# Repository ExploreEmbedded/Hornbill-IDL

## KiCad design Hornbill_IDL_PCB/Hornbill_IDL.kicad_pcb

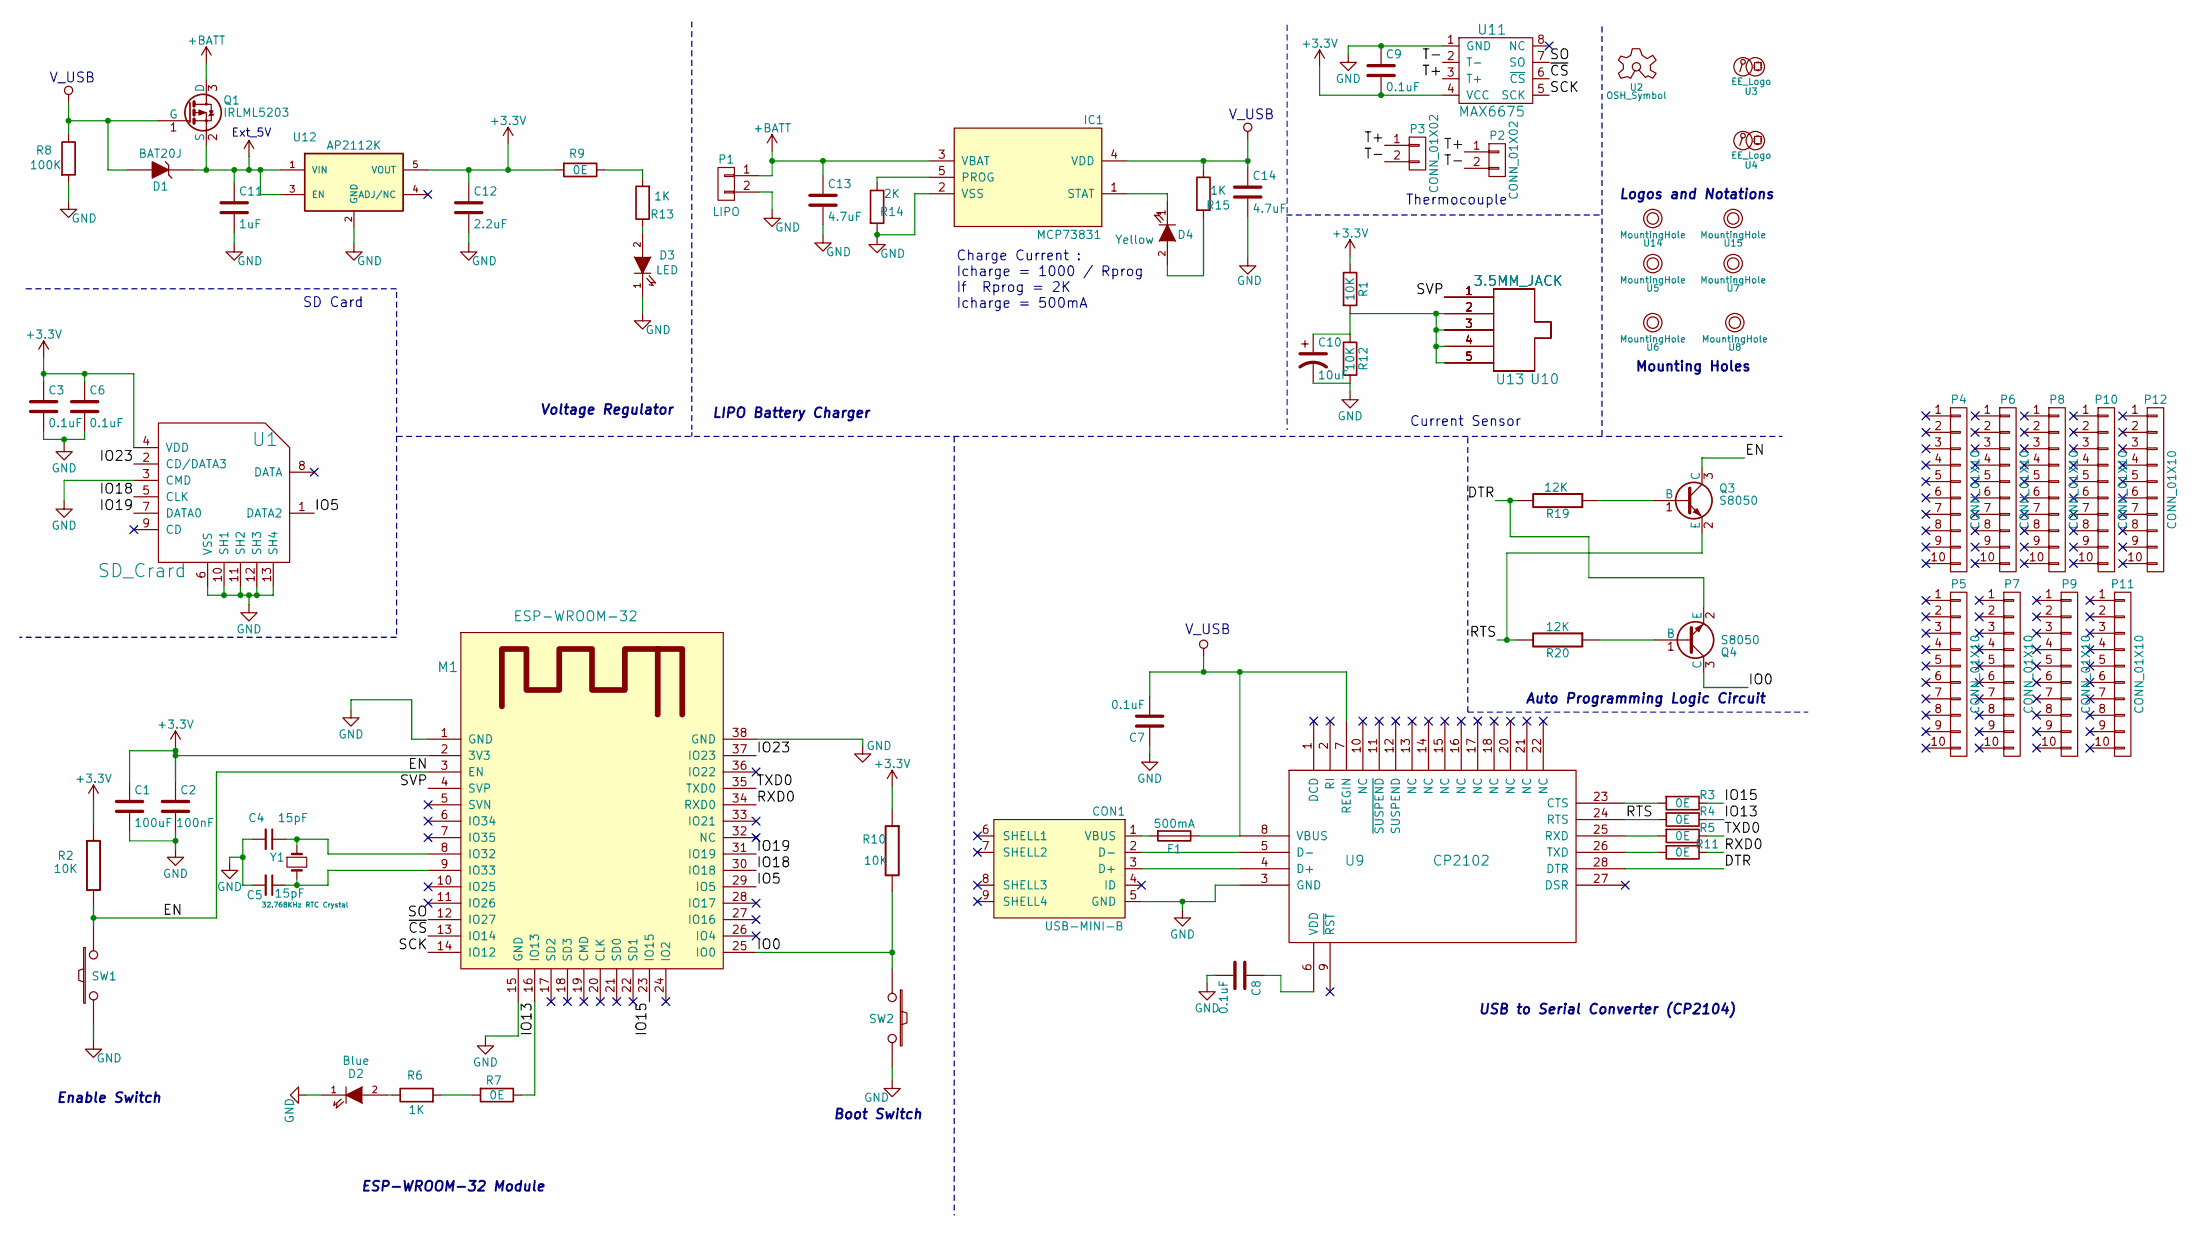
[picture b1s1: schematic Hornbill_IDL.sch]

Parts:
C1: 100uF; C_1206
C2: 100nF; C_0603
C3, C6, C7, C8: 0.1uF; C_0603
C4, C5: 15pF; C_0603
C9: 0.1uF; C_1206
C10: 10uF; CP_Radial_D4.0mm_P2.00mm
C11: 1uF; C_0603
C12: 2.2uF; C_0603
C13, C14: 4.7uF; C_0603
CON1: USB-MINI-B; USB_Micro-B_SMD_NEW_1
D1: BAT20J; SOD-80_diode_1
D2: Blue; LED-0603_NEW
D3: LED; LED-0603
D4: Yellow; LED-0603
F1: 500mA; Fuse_500mA
IC1: MCP73831; SOT-23-5
M1: ESP-WROOM-32; ESP-32S
P1: LIPO; JST_SMD
P2, P3: CONN_01X02; Thermocouple Connector
P4, P5, P6, P7, P8, P9, P10, P11, P12: CONN_01X10; Pin_Header_Straight_1x10_Pitch2.54mm
Q1: IRLML5203; SOT-23
Q3, Q4: S8050; SOT-23
R1, R2, R10, R12: 10K; R_0603
R3, R4, R5, R7, R9, R11: 0E; R_0603
R6, R13, R15: 1K; R_0603
R8: 100K; R_0603
R14: 2K; R_0603
R19, R20: 12K; R_0603
SW1, SW2: SW_PUSH; smd_push2_New
U1: SD_Crard; Micro_SD
U2: OSH_Symbol; Logo_silk_OSHW_6x6mm
U3: EE_Logo; Hornbill IDL
U4: EE_Logo; Logo_8
U5, U6, U7, U8, U14, U15: MountingHole; MountingHole_2.5mm
U9: CP2102; cp2102_xl2
U10, U13: 3.5MM_JACK; 3.5mm_Jack
U11: MAX6675; SOIC-8_3.9x4.9mm_Pitch1.27mm
U12: AP2112K; SOT-23-5
Y1: 32.768KHz RTC Crystal; SMD_RTC_Crstl

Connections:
+3V3: C1.1, C2.1, C3.1, C6.1, C9.2, C12.1, M1.2 (3V3), R1.1, R2.1, R9.2, R10.1, U1.4 (VDD), U11.4 (VCC), U12.5 (VOUT)
+5V: C11.1, D1.1 (K), Q1.2 (S), U12.1 (VIN), U12.3 (EN)
+BATT: C13.1, IC1.3 (VBAT), P1.1, Q1.3 (D)
/DTR: Q4.2 (E), R19.2, U9.28 (DTR)
/EN: M1.3 (EN), Q3.3 (C), R2.2, SW1.1
/IO0: M1.25 (IO0), Q4.3 (C), R10.2, SW2.1
/IO5: M1.29 (IO5), U1.1 (DATA2)
/IO13: M1.16 (IO13), R4.1, R7.1
/IO15: M1.23 (IO15), R3.1
/IO18: M1.30 (IO18), U1.5 (CLK)
/IO19: M1.31 (IO19), U1.7 (DATA0)
/IO23: M1.37 (IO23), U1.2 (CD/DATA3)
/RTS: Q3.2 (E), R4.2, R20.2, U9.24 (RTS)
/RXD0: M1.34 (RXD0), R11.1
/SCK: M1.14 (IO12), U11.5 (SCK)
/SO: M1.12 (IO27), U11.7 (SO)
/SVP: M1.4 (SVP), U10.1, U13.1
/T+: P2.1, P3.1, U11.3 (T+)
/T-: P2.2, P3.2, U11.2 (T-)
/TXD0: M1.35 (TXD0), R5.1
/~CS: M1.13 (IO14), U11.6 (~CS)
GND: C1.2, C2.2, C3.2, C4.2, C5.2, C6.2, C7.1, C8.2, C9.1, C10.2, C11.2, C12.2, C13.2, C14.2, CON1.5 (GND), D2.1 (K), D3.1 (K), IC1.2 (VSS), M1.1 (GND), M1.15 (GND), M1.38 (GND), P1.2, R8.2, R12.2, R14.2, SW1.2, SW2.2, U1.3 (CMD), U1.6 (VSS), U1.10 (SH1), U1.11 (SH2), U1.12 (SH3), U1.13 (SH4), U9.3 (GND), U11.1 (GND), U12.2 (GND)
unnamed: C4.1, M1.8 (IO32), Y1.1
unnamed: C5.1, M1.9 (IO33), Y1.2
unnamed: C8.1, U9.6 (VDD)
unnamed: C10.1, R1.2, R12.1, U10.2, U10.3, U10.4, U10.5, U13.2, U13.3, U13.4, U13.5
unnamed: CON1.1 (VBUS), F1.2
unnamed: CON1.2 (D-), U9.5 (D-)
unnamed: CON1.3 (D+), U9.4 (D+)
unnamed: D2.2 (A), R6.1
unnamed: D3.2 (A), R13.1
unnamed: D4.1 (K), IC1.1 (STAT)
unnamed: D4.2 (A), R15.2
unnamed: IC1.5 (PROG), R14.1
unnamed: Q3.1 (B), R19.1
unnamed: Q4.1 (B), R20.1
unnamed: R3.2, U9.23 (CTS)
unnamed: R5.2, U9.25 (RXD)
unnamed: R6.2, R7.2
unnamed: R11.2, U9.26 (TXD)
unnamed: R9.1, R13.2
VCC: C7.2, C14.1, D1.2 (A), F1.1, IC1.4 (VDD), Q1.1 (G), R8.1, R15.1, U9.7 (REGIN), U9.8 (VBUS)

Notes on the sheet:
Logos and Notations
Enable Switch
Boot Switch
Auto Programming Logic Circuit
ESP-WROOM-32 Module
USB to Serial Converter (CP2104)
Mounting Holes
V_USB
Ext_5V
Voltage Regulator
Charge Current : Icharge = 1000 / Rprog If Rprog = 2K Icharge = 500mA
LIPO Battery Charger
Thermocouple
Current Sensor
SD Card

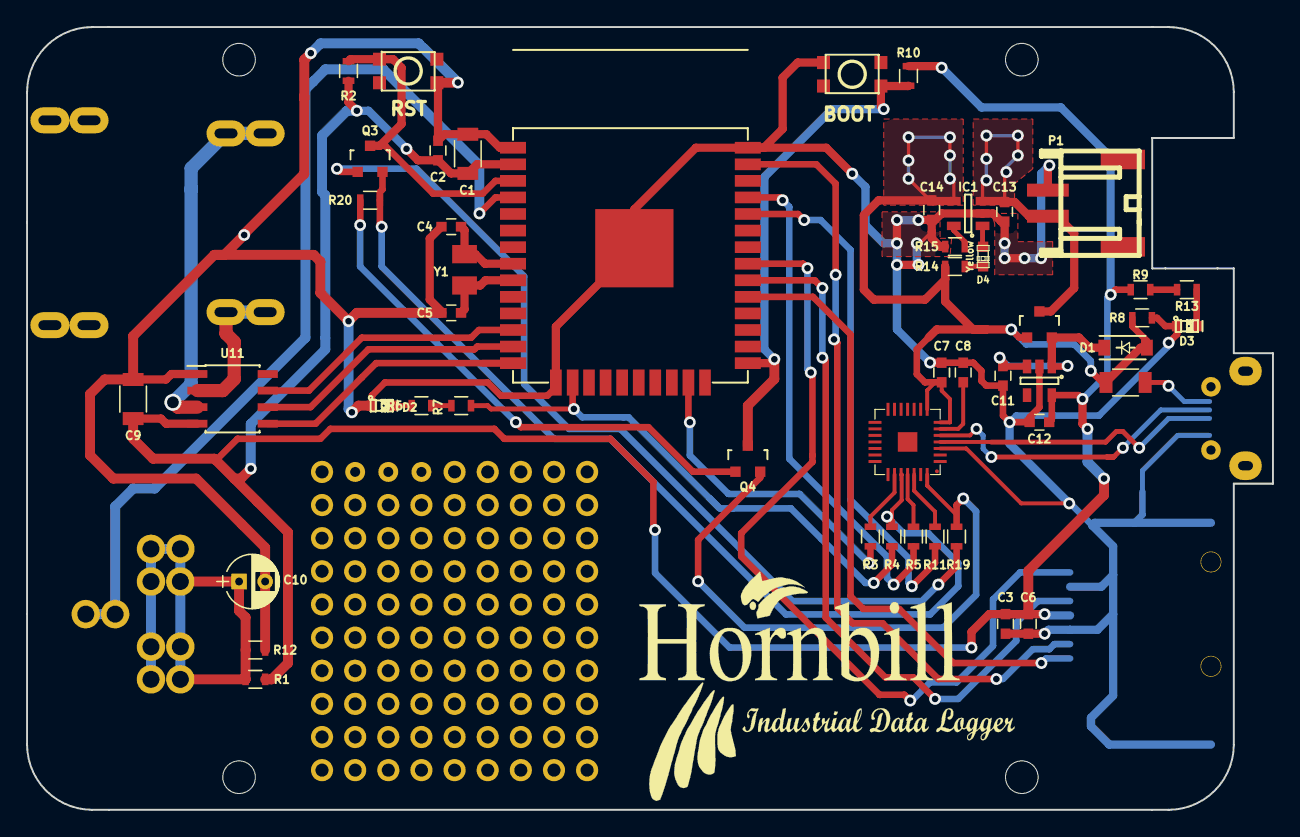
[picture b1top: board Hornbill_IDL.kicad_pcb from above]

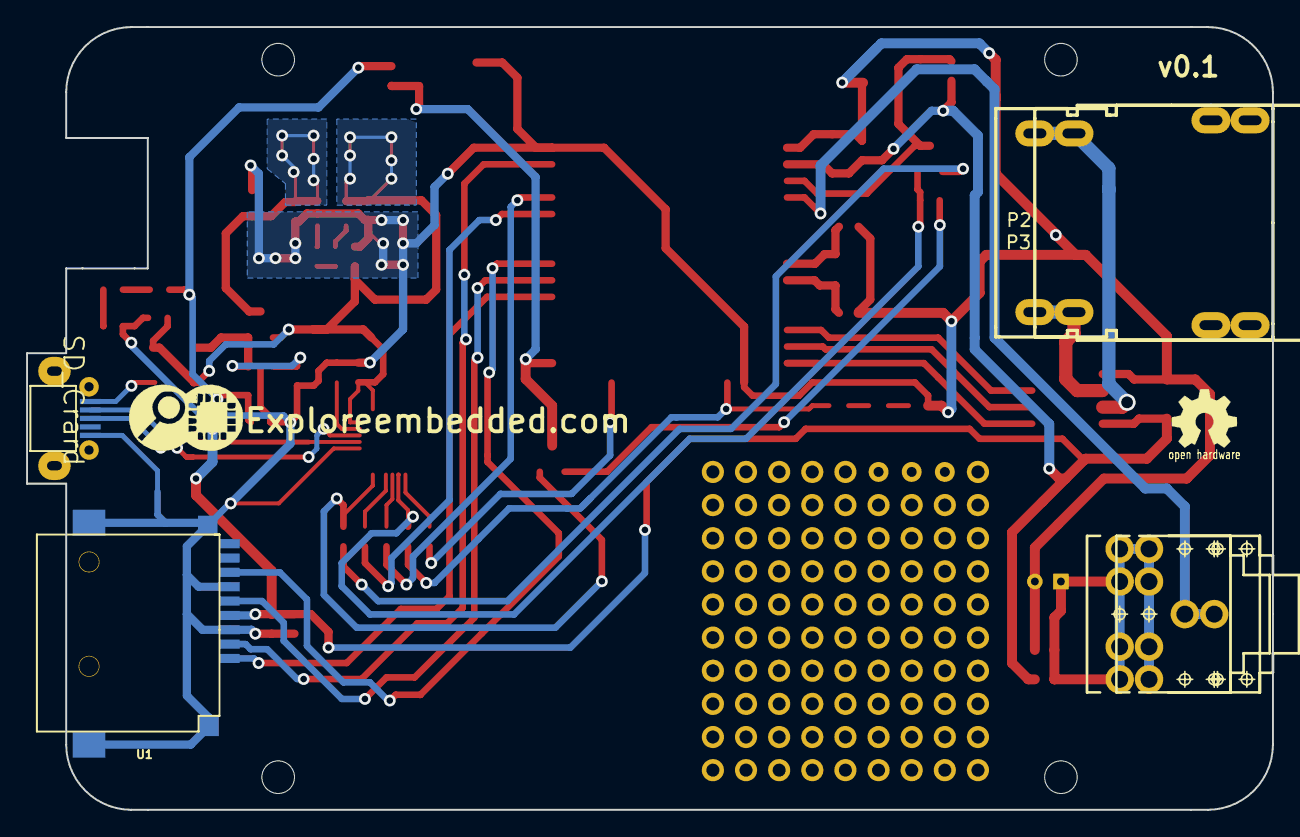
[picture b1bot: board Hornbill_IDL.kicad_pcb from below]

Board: 2 copper layers, 95.5 x 60.0 mm, 72 parts (8 on the bottom side), 42 nets.

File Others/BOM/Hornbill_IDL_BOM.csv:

Id,Designator,Package,Qty,Designation
3,D2,LED-0603,1,Blue
4,D3,LED-0603,1,LED
5,C1,C_1206,1,100uF
6,C2,C_0603,1,100nF
7,"C3,C6,C8,C7",C_0603,4,0.1uF
8,"C4,C5",C_0603,2,15pF
9,CON1,USB_Micro,1,USB-MINI-B
10,M1,ESP-32S,1,ESP-WROOM-32
11,"R2,R10,R1,R12",R_0603,4,10K
12,"R6,R13,R15",R_0603,3,1K
13,"R7,R9,R3,R4,R5,R11",R_0603,6,0E
14,R8,R_0603,1,100K
15,"R19,R20",R_0603,2,12K
16,"SW1,SW2",smd_push2_New,2,SW_PUSH
17,U2,Logo_silk_OSHW_6x6mm,1,OSH_Symbol
18,U4,Logo_8,1,EE_Logo
19,Y1,SMD_RTC_Crstl,1,32.768KHz RTC Crystal
20,"Q3,Q4",SOT-23,2,S8050
21,F1,Fuse_500mA,1,500mA
22,U9,QFN28,1,CP2102-GMR
23,C9,C_1206,1,0.1uF
24,"U10,U13",3.5mm_Jack,2,3.5MM_JACK
25,U11,SOIC-8_3.9x4.9mm_Pitch1.27mm,1,MAX6675
26,"P2,P3",Thermocouple Connector,2,CONN_01X02
27,U3,Hornbill IDL,1,EE_Logo
28,C10,CP_Radial_D4.0mm_P2.00mm,1,10uF
29,C11,C_0603,1,1uF
30,C12,C_0603,1,2.2uF
31,"C13,C14",C_0603,2,4.7uF
32,D1,SOD-80_diode_1,1,BAT20J
33,IC1,SOT-23-5,1,MCP73831
34,P1,JST_SMD,1,LIPO
35,Q1,SOT-23,1,IRLML5203
36,R14,R_0603,1,2K
37,U1,Micro_SD,1,SD_Crard
38,U12,SOT-23-5,1,AP2112K
39,D4,LED-0603,1,Yellow
,,,,

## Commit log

2017-05-03 Added Design
2017-05-04 Filled charger zone
2017-05-04 Gerber file generated for v0.1
2017-06-22 BOM and Process sheet added
